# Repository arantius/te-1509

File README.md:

The TE-1509 is a homebrew memory expansion card for the Sharp PC-1500 / TRS-80 PC-2 Pocket Computer device.

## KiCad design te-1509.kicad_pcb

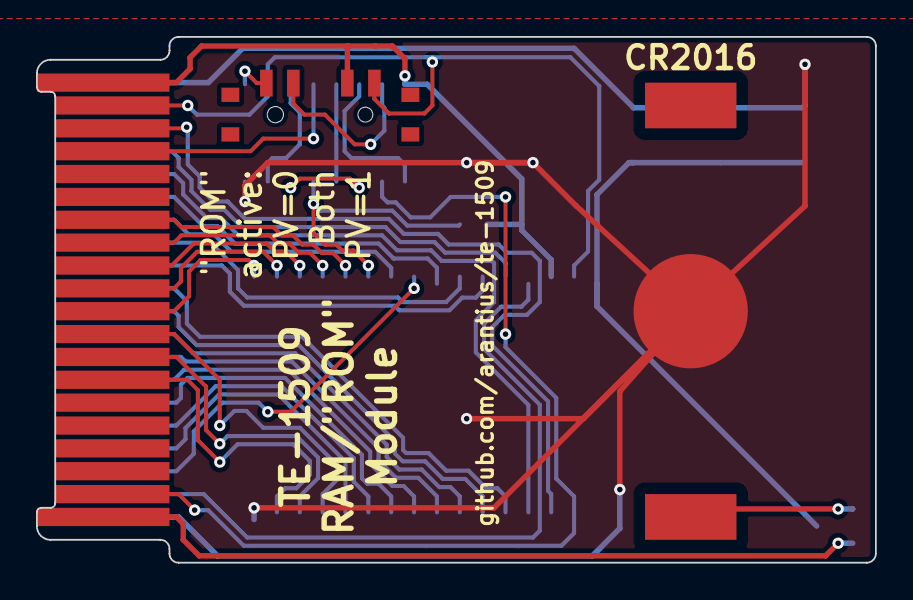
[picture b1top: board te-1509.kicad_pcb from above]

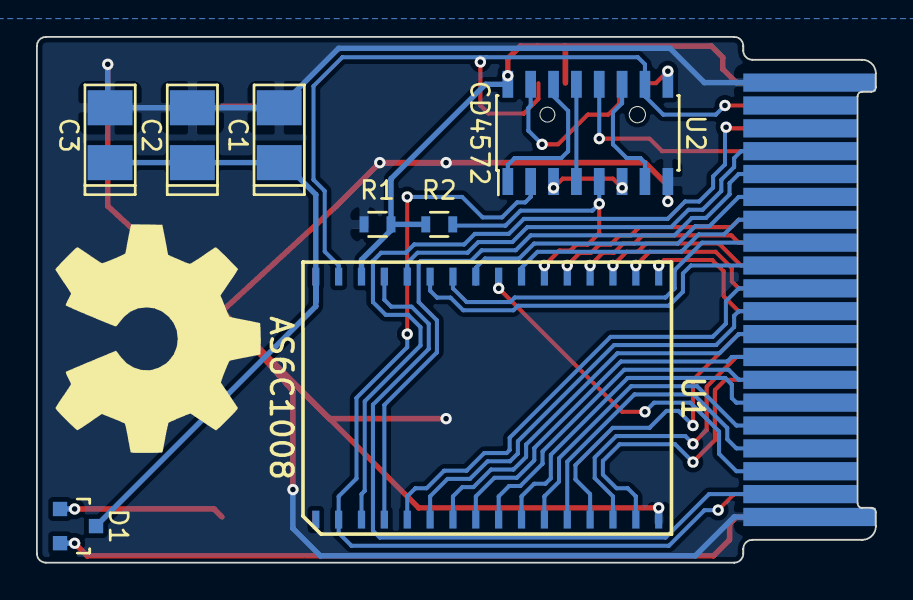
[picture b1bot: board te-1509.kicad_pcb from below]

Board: 2 copper layers, 46.6 x 29.2 mm, 11 parts (8 on the bottom side), 40 nets.

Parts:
BT1: BATTERY; Coin_20mm
C1, C2, C3: 33u; TantalC_SizeT_EIA-3528
CN1: ce-connector; CE_CONN
D1: BAT54C; SOT-23
R1, R2: 50k; R_0603
SW1: SP3T; EG1300
U1: AS6C1008; SOP32
U2: CD4572; SOIC-16_3.9x9.9mm_Pitch1.27mm

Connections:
/AD0: CN1.37, U1.12
/AD1: CN1.36, U1.11
/AD2: CN1.35, U1.10
/AD3: CN1.34, U1.9
/AD4: CN1.33, U1.8
/AD5: CN1.32, U1.7
/AD6: CN1.31, U1.6
/AD7: CN1.30, U1.5
/AD8: CN1.29, U1.27
/AD9: CN1.28, U1.26
/AD10: CN1.27, U1.23
/AD11: CN1.26, U1.25
/AD12: CN1.25, U1.4
/AD13: CN1.24, U1.28
/BSW: SW1.1, U2.15
/BT+: BT1.1, D1.1
/D0: CN1.14, U1.15
/D1: CN1.13, U1.14
/D2: CN1.12, U1.13
/D3: CN1.11, U1.17
/D4: CN1.10, U1.18
/D5: CN1.9, U1.19
/D6: CN1.8, U1.20
/D7: CN1.7, U1.21
/PU: CN1.3, U1.3
/PV: CN1.2, SW1.2, U1.31, U2.10
/RE: U2.3, U2.6
/VCC: CN1.1, R1.1, R2.1, SW1.3, U1.30, U2.16
/VGG: CN1.20, D1.2
/VRR: C1.1, C2.1, C3.1, D1.3, U1.32
/Y0: U2.7, U2.11
/Y2: U2.1, U2.14
/~CE: R2.2, U1.22, U2.5
/~OD: CN1.38, U1.24
/~PV: SW1.4, U2.9
/~RE: U2.4, U2.13
/~WE: CN1.39, U1.29
/~Y0: CN1.4, U2.12
/~Y2: CN1.19, U1.2, U2.2
GND: BT1.2, C1.2, C2.2, C3.2, CN1.21, CN1.40, R1.2, U1.16, U2.8

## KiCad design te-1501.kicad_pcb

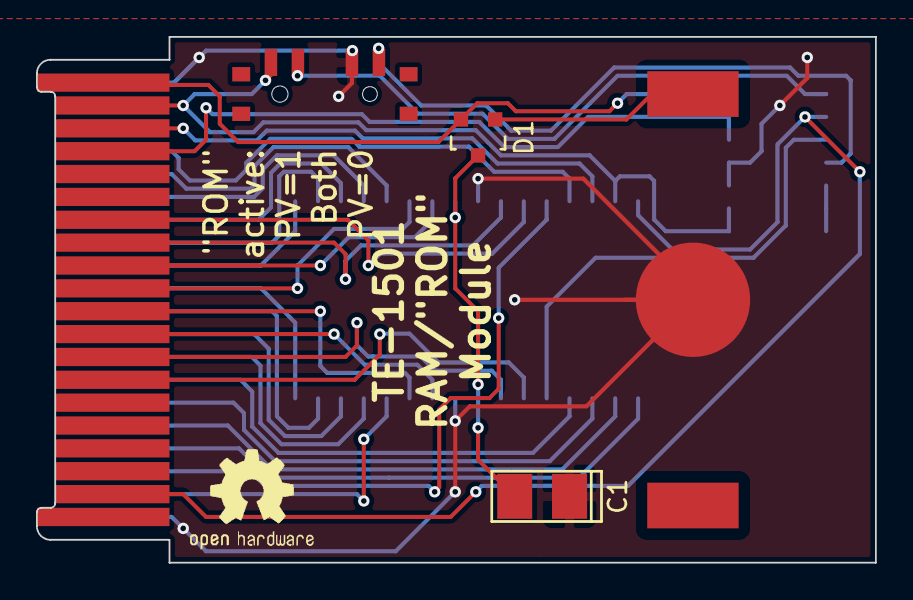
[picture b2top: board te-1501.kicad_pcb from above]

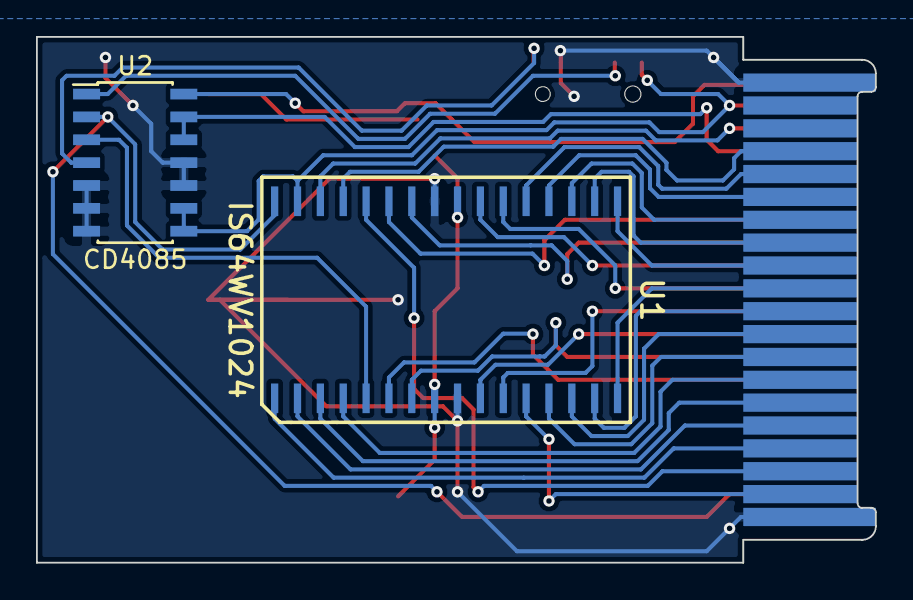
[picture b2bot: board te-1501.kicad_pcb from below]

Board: 2 copper layers, 46.6 x 29.2 mm, 8 parts (2 on the bottom side), 35 nets.

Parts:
BT1: BATTERY; CR2032
C1: 220u; TantalC_SizeT_EIA-3528
CN1: ce-connector; CE_CONN
D1: BAT54C; SOT-23
OSHW_LOGO: LOGO; OSHWLOGO0.3IN
SW1: SP3T; EG1300
U1: IS64WV1024; TSOP_II_32
U2: CD4085; SOIC-14_3.9x8.7mm_Pitch1.27mm

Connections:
/AD0: CN1.37, U1.1
/AD1: CN1.36, U1.2
/AD2: CN1.35, U1.3
/AD3: CN1.34, U1.4
/AD4: CN1.33, U1.13
/AD5: CN1.32, U1.14
/AD6: CN1.31, U1.15
/AD7: CN1.30, U1.16
/AD8: CN1.29, U1.17
/AD9: CN1.28, U1.18
/AD10: CN1.27, U1.19
/AD11: CN1.26, U1.20
/AD12: CN1.25, U1.21
/AD13: CN1.24, U1.29
/BANK8: SW1.1, U2.1
/BT+: BT1.1, D1.1
/D0: CN1.14, U1.6
/D1: CN1.13, U1.7
/D2: CN1.12, U1.10
/D3: CN1.11, U1.11
/D4: CN1.10, U1.22
/D5: CN1.9, U1.23
/D6: CN1.8, U1.26
/D7: CN1.7, U1.27
/PU: CN1.3, U1.30
/PV: CN1.2, SW1.4, U1.31, U2.8, U2.9
/VRR: C1.2, D1.3, U1.8, U1.24
/~CE: U1.5, U2.3
/~OD: CN1.38, U1.28
/~PV: SW1.2, U2.4
/~WE: CN1.39, U1.12
/~Y0: CN1.4, U2.12, U2.13
/~Y2: CN1.19, U1.32, U2.2
GND: BT1.2, C1.1, CN1.21, CN1.40, SW1.3, U1.9, U1.25, U2.5, U2.6, U2.7, U2.10, U2.11
VCC: CN1.1, D1.2, U2.14

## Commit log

2015-05-01 First TE-1501 version.
2015-05-01 Add readme, gerbers.
2015-05-01 add LICENSE
2015-05-02 Rename 1501 -> 1509
2015-05-02 Completely rework with a 5V compatible SRAM (D'oh!).
    Not to mention correct active-low select logic.
2015-05-03 routing tweaks
2015-05-03 switch to aluminum capacitor
2015-05-03 relocate bank switch logic
    fits better zoomed in on a wide screen
2015-05-07 switch to thinner cr2016, back to tantalum cap(s)
2015-05-07 pullup/pulldown sram enable resistors
2015-05-08 Switch to VGG as appropriate.
    The VGG supply is on 100% of the time. Keep SRAM powered from it,
    saving the lithium backup. The VCC supply switches on and off with the
    power controls, so power the rest of the circuitry from that.
2015-05-09 tweak footprints based on physical components
